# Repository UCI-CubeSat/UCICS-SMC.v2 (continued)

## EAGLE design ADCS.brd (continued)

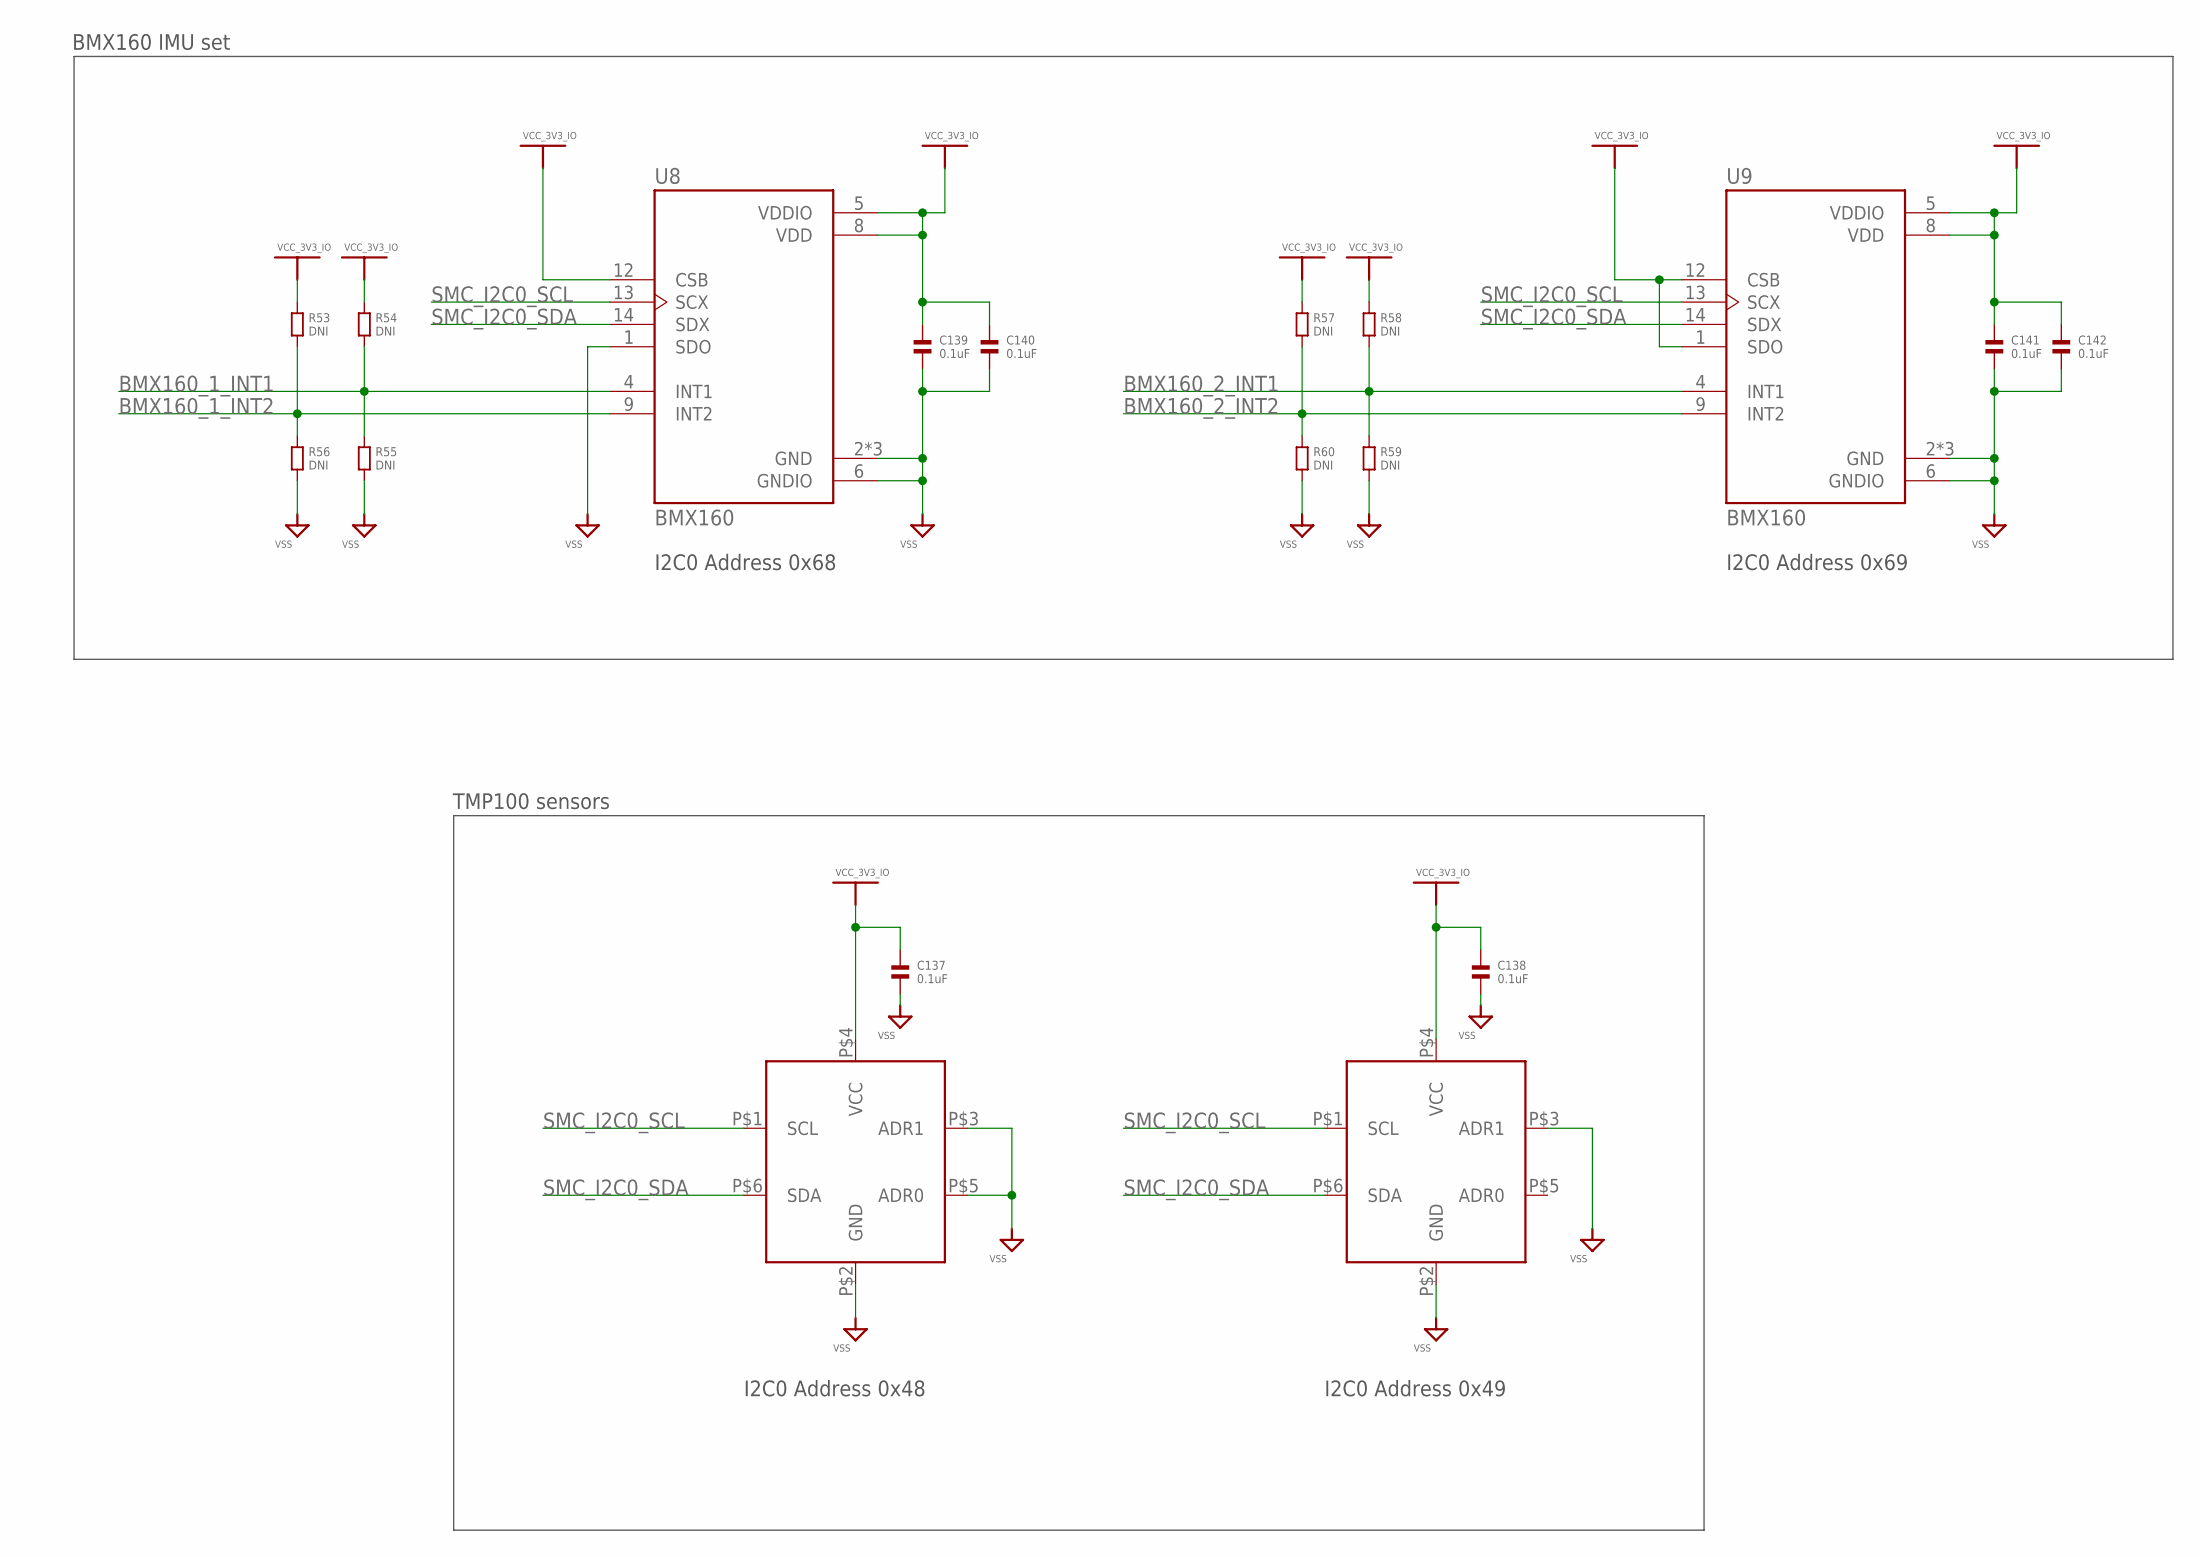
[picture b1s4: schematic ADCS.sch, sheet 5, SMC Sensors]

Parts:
C137, C138, C139, C140, C141, C142: 0.1uF; 0603
R53, R54, R55, R56, R57, R58, R59, R60: DNI; 0603
U7, U34: TMP100; SOT23-6
U8, U9: BMX160; PQFN50P250X300X100-14N

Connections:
BMX160_1_INT1: R54.2, R55.1, U8.4 (INT1); also elsewhere on the board
BMX160_1_INT2: R53.2, R56.1, U8.9 (INT2); also elsewhere on the board
BMX160_2_INT1: R58.2, R59.1, U9.4 (INT1); also elsewhere on the board
BMX160_2_INT2: R57.2, R60.1, U9.9 (INT2); also elsewhere on the board
SMC_I2C0_SCL: U7.P$1 (SCL), U8.13 (SCX), U9.13 (SCX), U34.P$1 (SCL); also elsewhere on the board
SMC_I2C0_SDA: U7.P$6 (SDA), U8.14 (SDX), U9.14 (SDX), U34.P$6 (SDA); also elsewhere on the board
VCC_3V3_IO: C137.1, C138.1, C139.1, C140.1, C141.1, C142.1, R53.1, R54.1, R57.1, R58.1, U7.P$4 (VCC), U8.5 (VDDIO), U8.8 (VDD), U8.12 (CSB), U9.1 (SDO), U9.5 (VDDIO), U9.8 (VDD), U9.12 (CSB), U34.P$4 (VCC); also elsewhere on the board
VSS: C137.2, C138.2, C139.2, C140.2, C141.2, C142.2, R55.2, R56.2, R59.2, R60.2, U7.P$2 (GND), U7.P$3 (ADR1), U8.1 (SDO), U8.2 (GND), U8.3 (GND), U8.6 (GNDIO), U8.7 (GND), U9.2 (GND), U9.3 (GND), U9.6 (GNDIO), U9.7 (GND), U34.P$2 (GND), U34.P$3 (ADR1), U34.P$5 (ADR0); also elsewhere on the board

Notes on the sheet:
I2C0 Address 0x48
I2C0 Address 0x49
TMP100 sensors
I2C0 Address 0x68
I2C0 Address 0x69
BMX160 IMU set

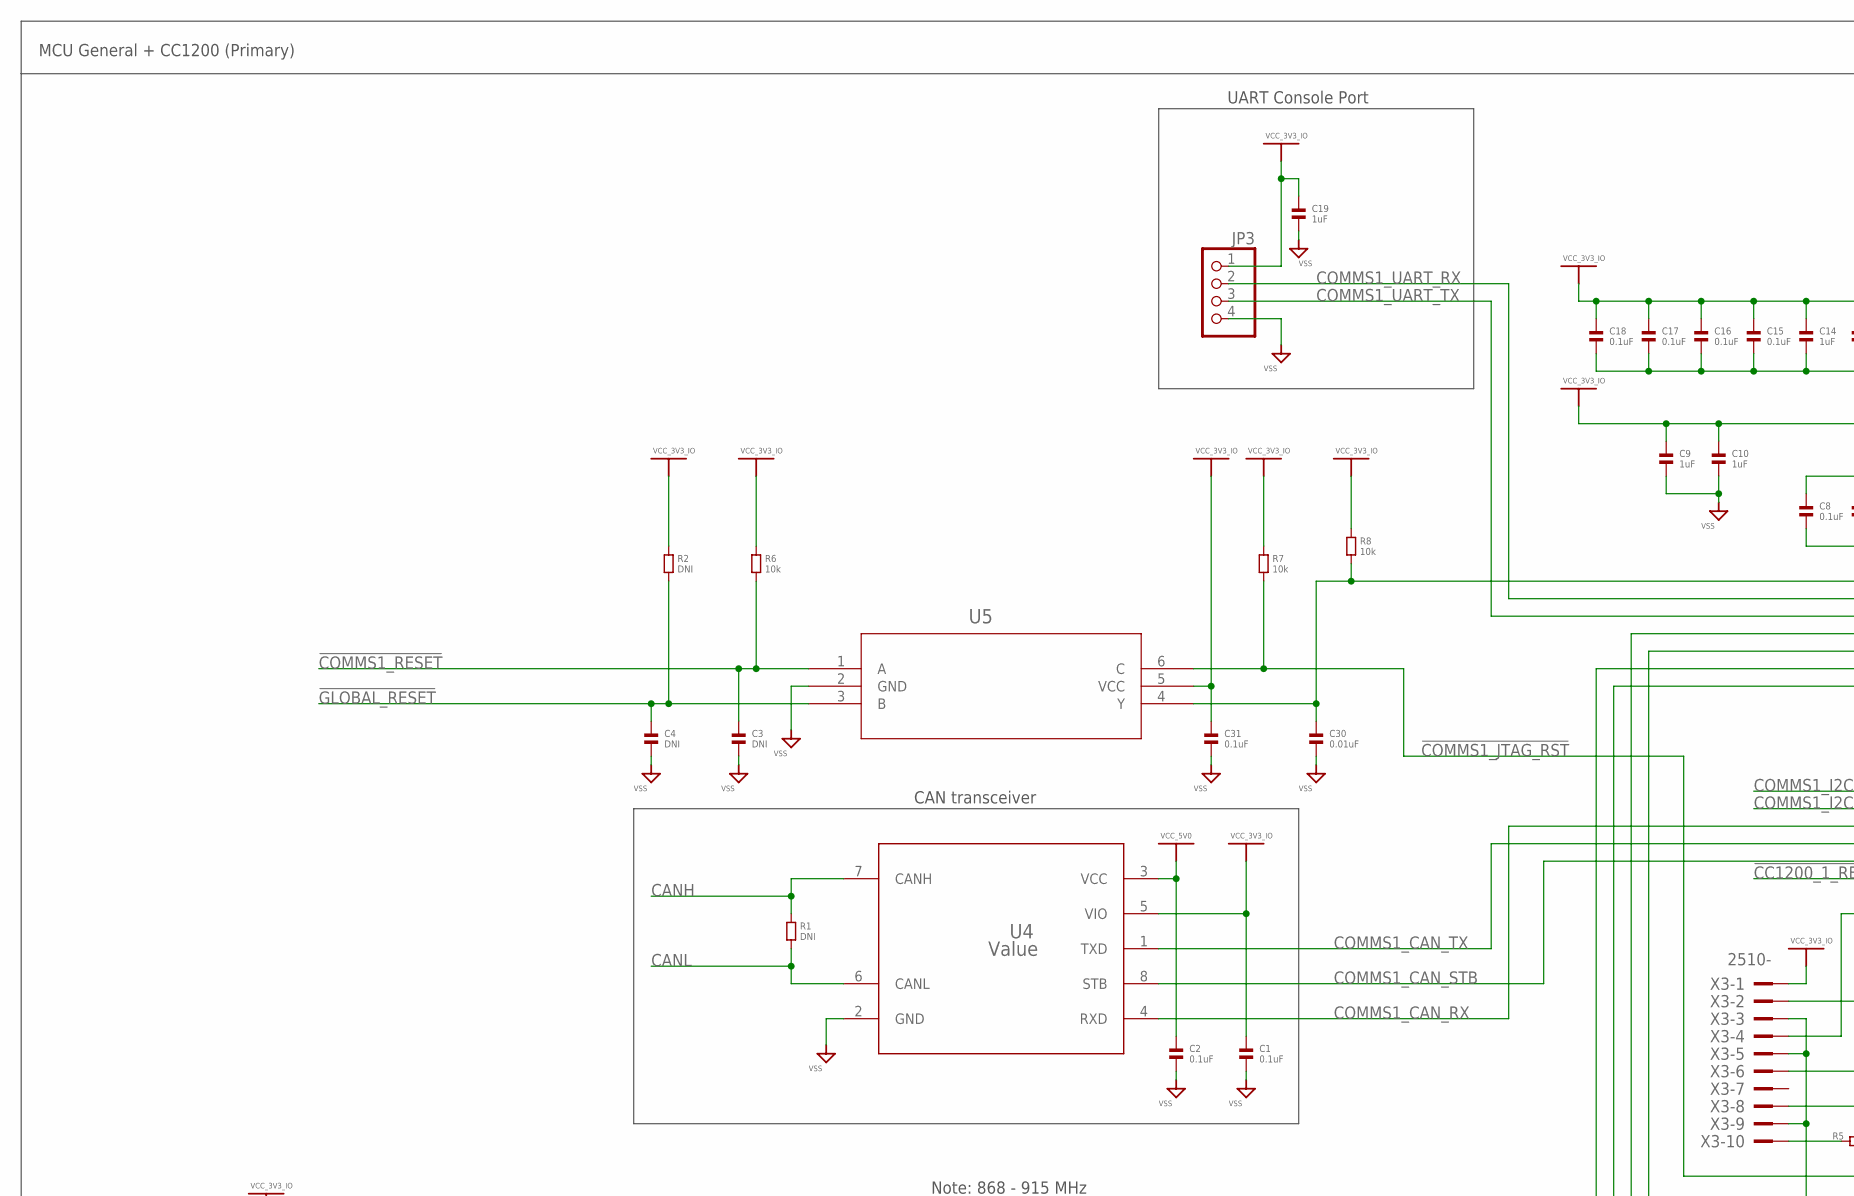
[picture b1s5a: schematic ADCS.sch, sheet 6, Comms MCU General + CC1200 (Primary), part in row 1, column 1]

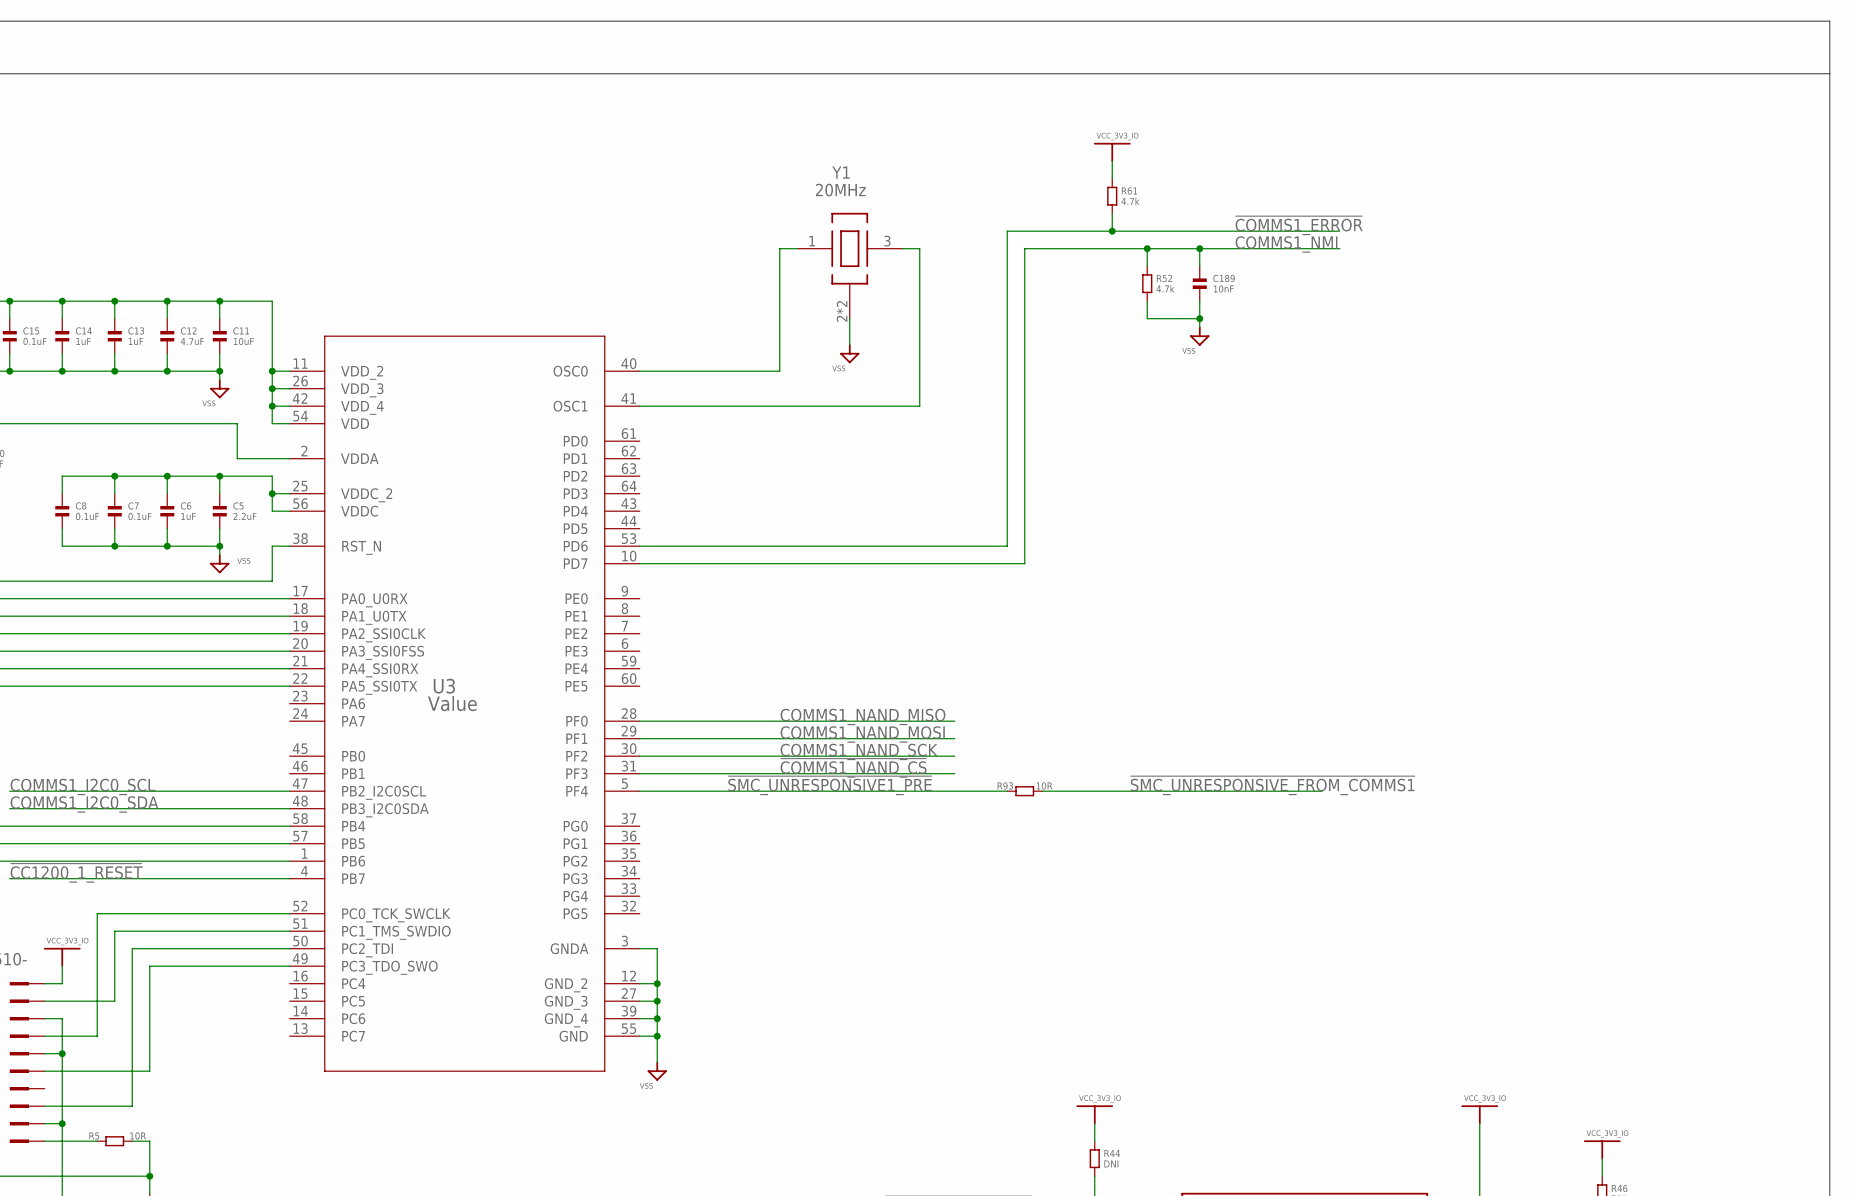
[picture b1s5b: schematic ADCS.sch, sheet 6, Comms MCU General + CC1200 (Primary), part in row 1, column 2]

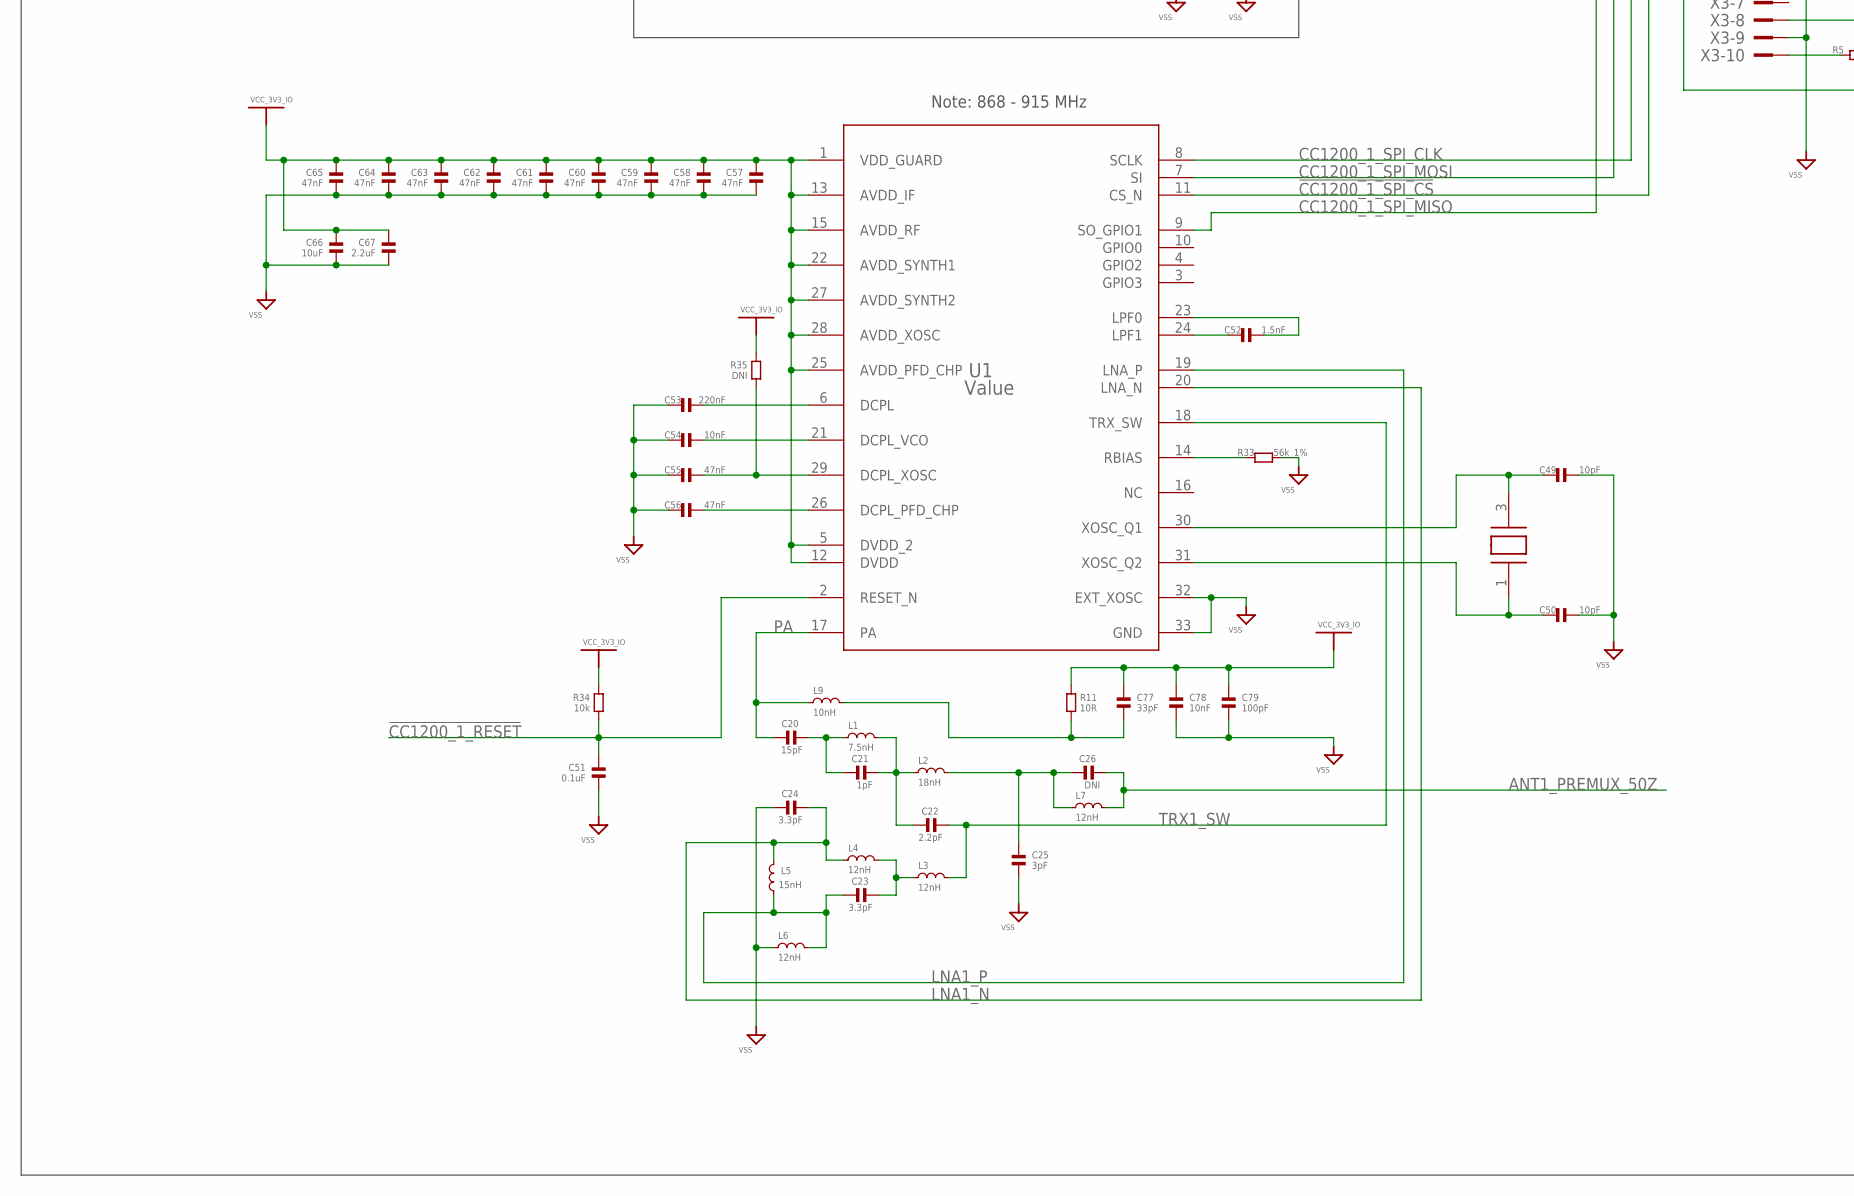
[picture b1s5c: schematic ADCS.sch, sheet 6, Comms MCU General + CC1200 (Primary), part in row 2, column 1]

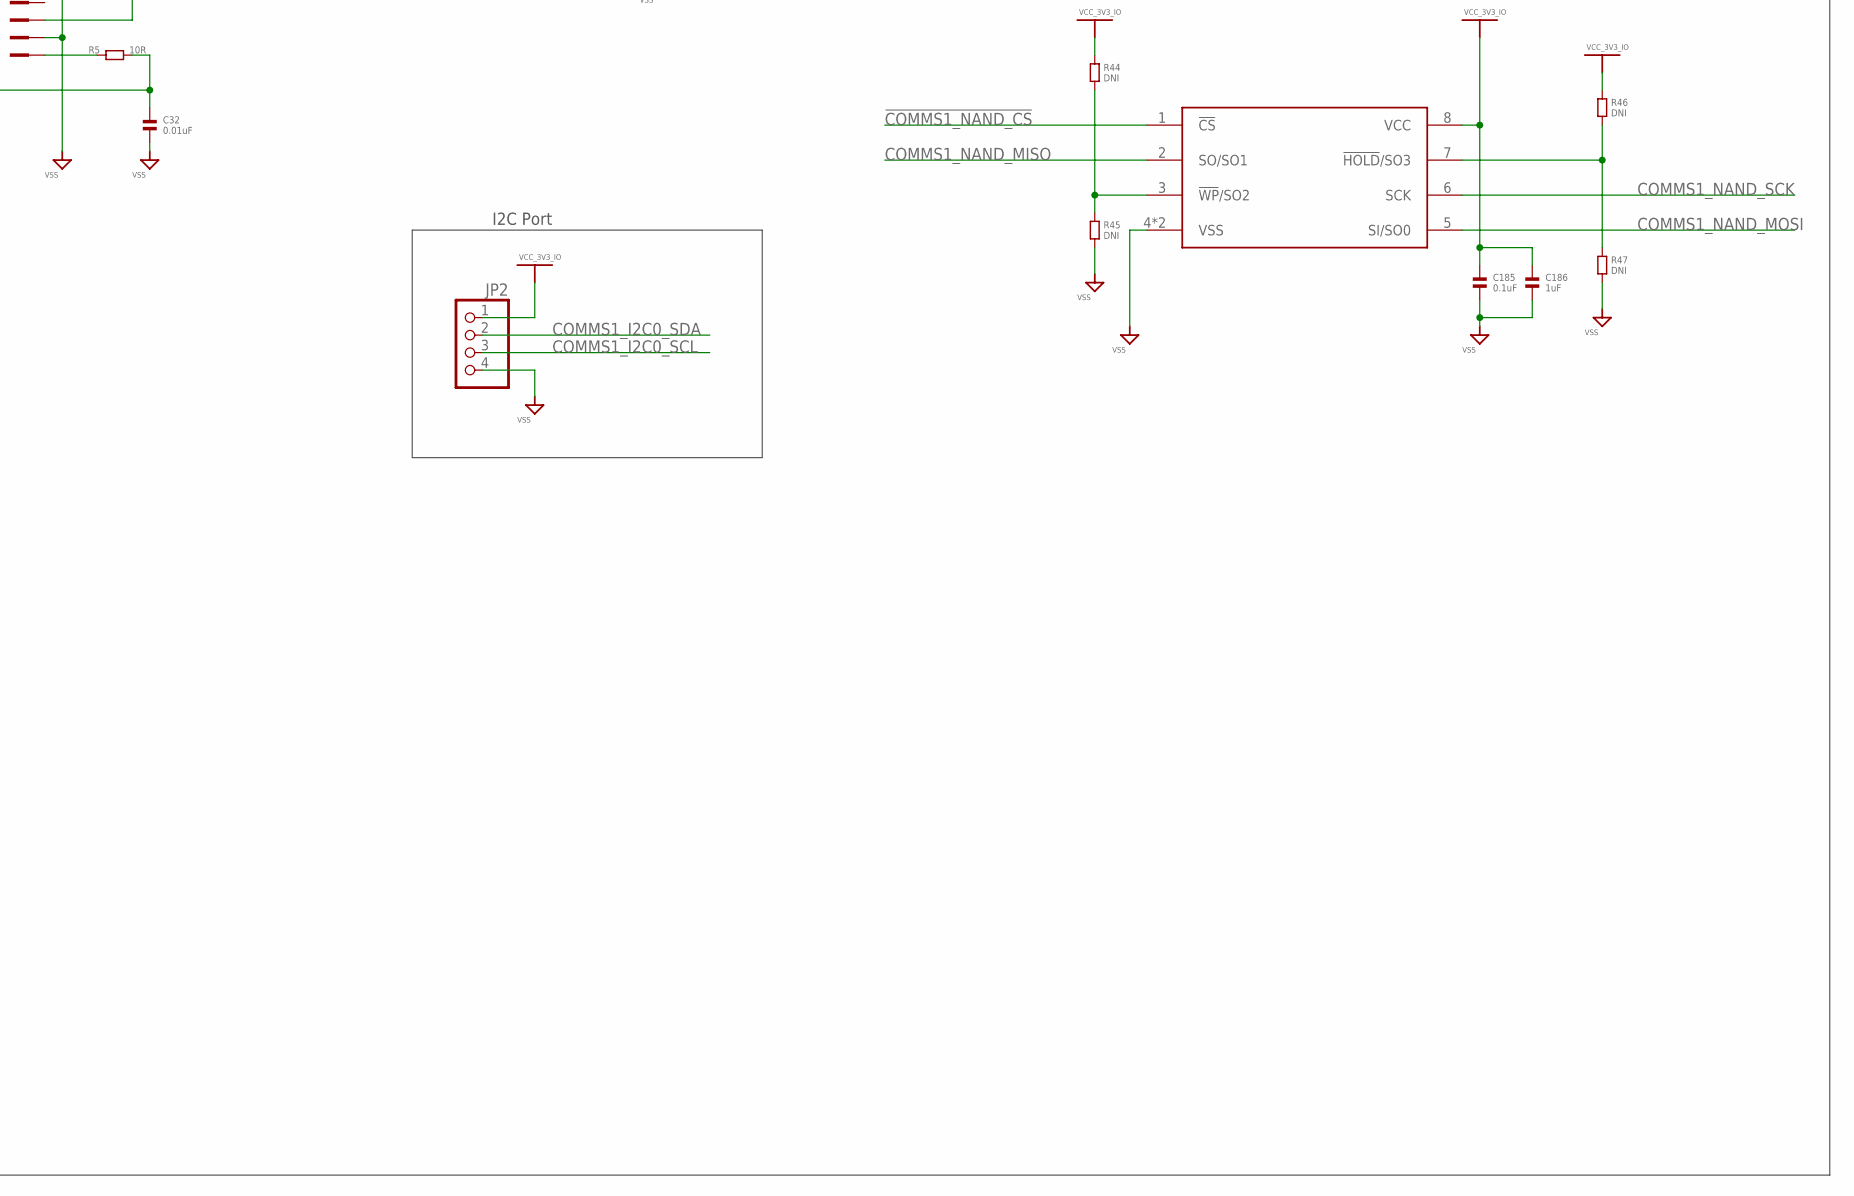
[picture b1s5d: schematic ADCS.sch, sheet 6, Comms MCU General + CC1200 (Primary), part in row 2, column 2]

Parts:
C1, C2, C7, C8, C15, C16, C17, C18, C31, C51, C185: 0.1uF; 0603
C3, C4: DNI; 0603
C5, C67: 2.2uF; 0603
C6, C9, C10, C13, C14, C19, C186: 1uF; 0603
C11, C66: 10uF; 0603
C12: 4.7uF; 0603
C20: 15pF; 0402
C21: 1pF; 0402
C22: 2.2pF; 0402
C23, C24: 3.3pF; 0402
C25: 3pF; 0402
C26: DNI; 0402
C30, C32: 0.01uF; 0603
C49, C50: 10pF; 0603
C52: 1.5nF; 0402
C53: 220nF; 0402
C54, C78: 10nF; 0402
C55, C56, C57, C58, C59, C60, C61, C62, C63, C64, C65: 47nF; 0402
C77: 33pF; 0402
C79: 100pF; 0402
C189: 10nF; 0603
JP2, JP3: PINHD-1X4; 1X04
L1: 7.5nH; 0402
L2: 18nH; 0402
L3, L4, L6, L7: 12nH; 0402
L5: 15nH; 0402
L9: 10nH; 0402
R1, R2, R44, R45, R46, R47: DNI; 0603
R5, R93: 10R; 0603
R6, R7, R8, R34: 10k; 0603
R11: 10R; 0402
R33: 56k_1%; 0603
R35: DNI; 0402
R52, R61: 4.7k; 0603
U1: Value; TEXAS_INSTRUMENTS-RADAR-CC1200RHBR
U3: Value; PM0064A_N
U4: Value; TEXAS_INSTRUMENTS-CAN_TRANSCEIVER-TCAN1042/LED_DRIVER-TLC59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
U5: TEXAS_INSTRUMENTS-AND_GATE-SN74LVC1G11_DCK_6
U15: KIOXIA_AMERICA-NAND_FLASH-TC58CVG0S3HRAIG
X1: ECS_INC-OSCILLATOR-ECS-400-10-37-CKM-TR
X3: 2510-; PAK100/2500-10
Y1: 20MHz; ESC-OSCILLATOR-ECS_200_9_33B_CTP_TR

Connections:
!CC1200_1_RESET: C51.1, R34.2, U1.2 (RESET_N), U3.4 (PB7)
!CC1200_1_SPI_CS: U1.11 (CS_N), U3.20 (PA3_SSI0FSS)
!COMMS1_ERROR: R61.2, U3.53 (PD6); also elsewhere on the board
!COMMS1_JTAG_RST: C32.1, R5.2, R7.2, U5.6 (C)
!COMMS1_NAND_CS: U3.31 (PF3), U15.1 (!CS)
!COMMS1_RESET: C3.1, R6.2, U5.1 (A); also elsewhere on the board
!GLOBAL_RESET: C4.1, R2.2, U5.3 (B); also elsewhere on the board
!SMC_UNRESPONSIVE1_PRE: R93.1, U3.5 (PF4)
!SMC_UNRESPONSIVE_FROM_COMMS1: R93.2; also elsewhere on the board
ANT1_PREMUX_50Z: C26.2, L7.2; also elsewhere on the board
CANH: R1.1, U4.7 (CANH); also elsewhere on the board
CANL: R1.2, U4.6 (CANL); also elsewhere on the board
CC1200_1_SPI_CLK: U1.8 (SCLK), U3.19 (PA2_SSI0CLK)
CC1200_1_SPI_MISO: U1.9 (SO_GPIO1), U3.21 (PA4_SSI0RX)
CC1200_1_SPI_MOSI: U1.7 (SI), U3.22 (PA5_SSI0TX)
COMMS1_CAN_RX: U3.58 (PB4), U4.4 (RXD)
COMMS1_CAN_STB: U3.1 (PB6), U4.8 (STB)
COMMS1_CAN_TX: U3.57 (PB5), U4.1 (TXD)
COMMS1_I2C0_SCL: JP2.3, U3.47 (PB2_I2C0SCL)
COMMS1_I2C0_SDA: JP2.2, U3.48 (PB3_I2C0SDA)
COMMS1_NAND_MISO: U3.28 (PF0), U15.2 (SO/SO1)
COMMS1_NAND_MOSI: U3.29 (PF1), U15.5 (SI/SO0)
COMMS1_NAND_SCK: U3.30 (PF2), U15.6 (SCK)
COMMS1_NMI: C189.1, R52.1, U3.10 (PD7); also elsewhere on the board
COMMS1_UART_RX: JP3.2, U3.17 (PA0_U0RX); also elsewhere on the board
COMMS1_UART_TX: JP3.3, U3.18 (PA1_U0TX); also elsewhere on the board
LNA1_N: C24.2, L4.1, L5.2, U1.20 (LNA_N)
LNA1_P: C23.1, L5.1, L6.2, U1.19 (LNA_P)
unnamed: C5.1, C6.1, C7.1, C8.1, U3.25 (VDDC_2), U3.56 (VDDC)
unnamed: U3.40 (OSC0), Y1.1 (XI)
unnamed: U3.41 (OSC1), Y1.3 (XO)
unnamed: C20.2, C21.1, L1.1
unnamed: C23.2, L3.1, L4.2
unnamed: C21.2, C22.1, L1.2, L2.1
unnamed: C25.1, C26.1, L2.2, L7.1
unnamed: C77.2, L9.2, R11.2
unnamed: R44.2, R45.1, U15.3 (!WP!/SO2)
unnamed: R5.1, X3.10
unnamed: C30.1, R8.2, U3.38 (RST_N), U5.4 (Y)
unnamed: U3.50 (PC2_TDI), X3.8
unnamed: R33.1, U1.14 (RBIAS)
unnamed: C49.1, U1.30 (XOSC_Q1), X1.3 (XO)
unnamed: C50.1, U1.31 (XOSC_Q2), X1.1 (XI)
unnamed: U3.49 (PC3_TDO_SWO), X3.6
unnamed: U3.51 (PC1_TMS_SWDIO), X3.2
unnamed: U3.52 (PC0_TCK_SWCLK), X3.4
unnamed: C52.1, U1.24 (LPF1)
unnamed: C52.2, U1.23 (LPF0)
unnamed: C56.2, U1.26 (DCPL_PFD_CHP)
unnamed: C55.2, R35.2, U1.29 (DCPL_XOSC)
unnamed: C54.2, U1.21 (DCPL_VCO)
unnamed: C53.2, U1.6 (DCPL)
unnamed: R46.2, R47.1, U15.7 (!HOLD!/SO3)
PA: C20.1, L9.1, U1.17 (PA); also elsewhere on the board
TRX1_SW: C22.2, L3.2, U1.18 (TRX_SW)
VCC_3V3_IO: C1.1, C9.1, C10.1, C11.1, C12.1, C13.1, C14.1, C15.1, C16.1, C17.1, C18.1, C19.1, C31.1, C57.1, C58.1, C59.1, C60.1, C61.1, C62.1, C63.1, C64.1, C65.1, C66.1, C67.1, C77.1, C78.1, C79.1, C185.1, C186.1, JP2.1, JP3.1, R2.1, R6.1, R7.1, R8.1, R11.1, R34.1, R35.1, R44.1, R46.1, R61.1, U1.1 (VDD_GUARD), U1.5 (DVDD_2), U1.12 (DVDD), U1.13 (AVDD_IF), U1.15 (AVDD_RF), U1.22 (AVDD_SYNTH1), U1.25 (AVDD_PFD_CHP), U1.27 (AVDD_SYNTH2), U1.28 (AVDD_XOSC), U3.2 (VDDA), U3.11 (VDD_2), U3.26 (VDD_3), U3.42 (VDD_4), U3.54 (VDD), U4.5 (VIO), U5.5 (VCC), U15.8 (VCC), X3.1; also elsewhere on the board
VCC_5V0: C2.1, U4.3 (VCC); also elsewhere on the board
VSS: C1.2, C2.2, C3.2, C4.2, C5.2, C6.2, C7.2, C8.2, C9.2, C10.2, C11.2, C12.2, C13.2, C14.2, C15.2, C16.2, C17.2, C18.2, C19.2, C24.1, C25.2, C30.2, C31.2, C32.2, C49.2, C50.2, C51.2, C53.1, C54.1, C55.1, C56.1, C57.2, C58.2, C59.2, C60.2, C61.2, C62.2, C63.2, C64.2, C65.2, C66.2, C67.2, C78.2, C79.2, C185.2, C186.2, C189.2, JP2.4, JP3.4, L6.1, R33.2, R45.2, R47.2, R52.2, U1.32 (EXT_XOSC), U1.33 (GND), U3.3 (GNDA), U3.12 (GND_2), U3.27 (GND_3), U3.39 (GND_4), U3.55 (GND), U4.2 (GND), U5.2 (GND), U15.4 (VSS), U15.9 (VSS), X3.3, X3.5, X3.9, Y1.2 (VSS), Y1.4 (VSS); also elsewhere on the board

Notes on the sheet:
Note: 868 - 915 MHz
MCU General + CC1200 (Primary)
CAN transceiver
I2C Port
UART Console Port
